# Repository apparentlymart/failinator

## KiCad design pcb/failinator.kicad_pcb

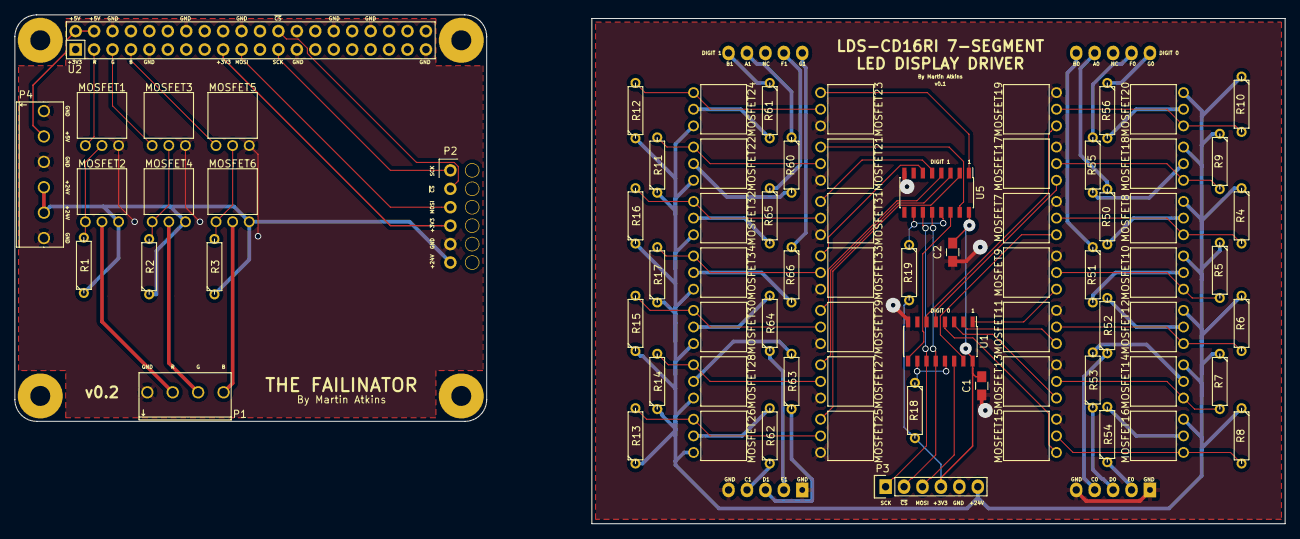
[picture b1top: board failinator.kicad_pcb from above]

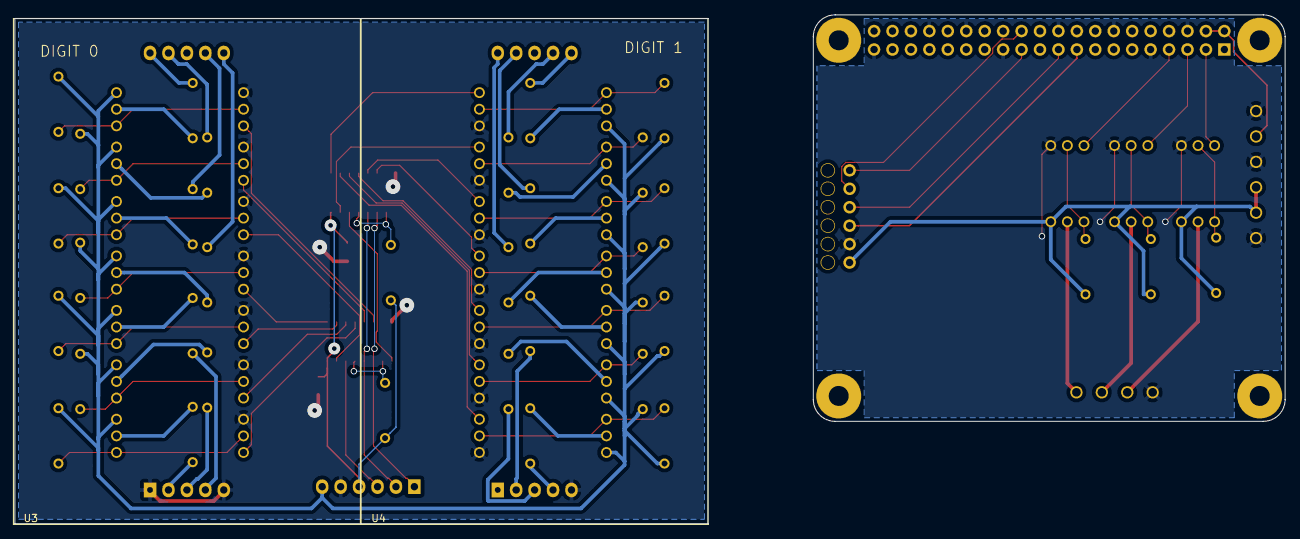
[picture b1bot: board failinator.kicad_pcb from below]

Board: 2 copper layers, 175.0 x 70.1 mm, 82 parts (2 on the bottom side), 81 nets.

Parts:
C1, C2: C_Small; C_0805_HandSoldering
MOSFET1, MOSFET3, MOSFET5, MOSFET7, MOSFET9, MOSFET11, MOSFET13, MOSFET15, MOSFET17, MOSFET19, MOSFET21, MOSFET23, MOSFET25, MOSFET27, MOSFET29, MOSFET31, MOSFET33: FQU13N06L; TO-251AA
MOSFET2, MOSFET4, MOSFET6, MOSFET8, MOSFET10, MOSFET12, MOSFET14, MOSFET16, MOSFET18, MOSFET20, MOSFET22, MOSFET24, MOSFET26, MOSFET28, MOSFET30, MOSFET32, MOSFET34: FQU17P06; TO-251AA
Mounting_Hole_2.75mm, Mounting_Hole_2.75mm#2, Mounting_Hole_2.75mm#3, Mounting_Hole_2.75mm#4: VAL**; Mounting_Hole_2.75mm
P1: CONN_01X04; TERM_4
P2: CONN_01X06; Wire_Conn_6pin_StrainReliefRight
P3: CONN_01X06; Pin_Header_Straight_1x06
P4: CONN_01X06; TERM_6
R1, R2, R3, R4, R5, R6, R7, R8, R9, R10, R11, R12, R13, R14, R15, R16, R17, R18, R19: 10k; R3
R50, R51, R52, R53, R54, R55, R56, R60, R61, R62, R63, R64, R65, R66: 150; R3
U1, U5: 74HC594; SOIC-16_3.9x9.9mm_Pitch1.27mm
U2: RASPIPLUSHEADER; Pin_Header_Straight_2x20
U3, U4: LDS-CD16RI

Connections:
+3V3: P2.4, U2.1, U2.17
+5V: P4.2, U2.2, U2.4
+24V: MOSFET2.3, MOSFET4.3, MOSFET6.3, P2.6, P4.4, P4.5, R1.1, R2.1, R3.1
/AmberDriver/EN: MOSFET3.1, U2.5
/AmberDriver/VOUT: MOSFET4.2, P1.3
/DISP_CS: P2.2, U2.24
/D_+3V3: C1.2, C2.2, P3.4, R18.2, R19.2, U1.16, U5.16
/D_DISP_CS: P3.2, U1.12, U5.12
/D_MOSI: P3.3, U1.14
/D_SCLK: P3.1, U1.11, U5.11
/DisplayDrivers/A0Driver/VOUT: MOSFET8.2, R50.2
/DisplayDrivers/A0_L: MOSFET7.1, U1.15
/DisplayDrivers/A0_P: R50.1, U3.7
/DisplayDrivers/A1Driver/VOUT: MOSFET22.2, R60.2
/DisplayDrivers/A1_L: MOSFET21.1, U5.15
/DisplayDrivers/A1_P: R60.1, U4.7
/DisplayDrivers/B0Driver/VOUT: MOSFET10.2, R51.2
/DisplayDrivers/B0_L: MOSFET9.1, U1.1
/DisplayDrivers/B0_P: R51.1, U3.6
/DisplayDrivers/B1Driver/VOUT: MOSFET24.2, R61.2
/DisplayDrivers/B1_L: MOSFET23.1, U5.1
/DisplayDrivers/B1_P: R61.1, U4.6
/DisplayDrivers/C0Driver/VOUT: MOSFET12.2, R52.2
/DisplayDrivers/C0_L: MOSFET11.1, U1.2
/DisplayDrivers/C0_P: R52.1, U3.4
/DisplayDrivers/C1Driver/VOUT: MOSFET26.2, R62.2
/DisplayDrivers/C1_L: MOSFET25.1, U5.2
/DisplayDrivers/C1_P: R62.1, U4.4
/DisplayDrivers/D0Driver/VOUT: MOSFET14.2, R53.2
/DisplayDrivers/D0_L: MOSFET13.1, U1.3
/DisplayDrivers/D0_P: R53.1, U3.3
/DisplayDrivers/D1Driver/VOUT: MOSFET28.2, R63.2
/DisplayDrivers/D1_L: MOSFET27.1, U5.3
/DisplayDrivers/D1_P: R63.1, U4.3
/DisplayDrivers/E0Driver/VOUT: MOSFET16.2, R54.2
/DisplayDrivers/E0_L: MOSFET15.1, U1.4
/DisplayDrivers/E0_P: R54.1, U3.2
/DisplayDrivers/E1Driver/VOUT: MOSFET30.2, R64.2
/DisplayDrivers/E1_L: MOSFET29.1, U5.4
/DisplayDrivers/E1_P: R64.1, U4.2
/DisplayDrivers/F0Driver/VOUT: MOSFET18.2, R55.2
/DisplayDrivers/F0_L: MOSFET17.1, U1.5
/DisplayDrivers/F0_P: R55.1, U3.9
/DisplayDrivers/F1Driver/VOUT: MOSFET32.2, R65.2
/DisplayDrivers/F1_L: MOSFET31.1, U5.5
/DisplayDrivers/F1_P: R65.1, U4.9
/DisplayDrivers/G0Driver/VOUT: MOSFET20.2, R56.2
/DisplayDrivers/G0_L: MOSFET19.1, U1.6
/DisplayDrivers/G0_P: R56.1, U3.10
/DisplayDrivers/G1Driver/VOUT: MOSFET34.2, R66.2
/DisplayDrivers/G1_L: MOSFET33.1, U5.6
/DisplayDrivers/G1_P: R66.1, U4.10
/DisplayDrivers/GND: C1.1, C2.1, MOSFET7.3, MOSFET9.3, MOSFET11.3, MOSFET13.3, MOSFET15.3, MOSFET17.3, MOSFET19.3, MOSFET21.3, MOSFET23.3, MOSFET25.3, MOSFET27.3, MOSFET29.3, MOSFET31.3, MOSFET33.3, P3.5, U1.8, U3.1, U3.5, U4.1, U4.5, U5.8
/DisplayDrivers/VIN: MOSFET8.3, MOSFET10.3, MOSFET12.3, MOSFET14.3, MOSFET16.3, MOSFET18.3, MOSFET20.3, MOSFET22.3, MOSFET24.3, MOSFET26.3, MOSFET28.3, MOSFET30.3, MOSFET32.3, MOSFET34.3, P3.6, R4.1, R5.1, R6.1, R7.1, R8.1, R9.1, R10.1, R11.1, R12.1, R13.1, R14.1, R15.1, R16.1, R17.1
/GreenDriver/EN: MOSFET5.1, U2.7
/GreenDriver/VOUT: MOSFET6.2, P1.4
/MOSI: P2.3, U2.19
/RedDriver/EN: MOSFET1.1, U2.3
/RedDriver/VOUT: MOSFET2.2, P1.2
/SCLK: P2.1, U2.23
GND: MOSFET1.3, MOSFET3.3, MOSFET5.3, P1.1, P2.5, P4.1, P4.3, P4.6, U2.6, U2.9, U2.14, U2.20, U2.25, U2.30, U2.34, U2.39
unnamed: MOSFET1.2, MOSFET2.1, R1.2
unnamed: MOSFET3.2, MOSFET4.1, R2.2
unnamed: MOSFET5.2, MOSFET6.1, R3.2
unnamed: MOSFET7.2, MOSFET8.1, R4.2
unnamed: MOSFET9.2, MOSFET10.1, R5.2
unnamed: MOSFET11.2, MOSFET12.1, R6.2
unnamed: MOSFET13.2, MOSFET14.1, R7.2
unnamed: MOSFET15.2, MOSFET16.1, R8.2
unnamed: MOSFET17.2, MOSFET18.1, R9.2
unnamed: MOSFET19.2, MOSFET20.1, R10.2
unnamed: MOSFET21.2, MOSFET22.1, R11.2
unnamed: MOSFET23.2, MOSFET24.1, R12.2
unnamed: MOSFET25.2, MOSFET26.1, R13.2
unnamed: MOSFET27.2, MOSFET28.1, R14.2
unnamed: MOSFET29.2, MOSFET30.1, R15.2
unnamed: MOSFET31.2, MOSFET32.1, R16.2
unnamed: MOSFET33.2, MOSFET34.1, R17.2
unnamed: R18.1, U1.10, U1.13
unnamed: R19.1, U5.10, U5.13
unnamed: U1.9, U5.14

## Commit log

2015-09-25 KiCad project.
2015-09-25 Schematic
2015-09-25 Pi Hat PCB mounting hole footprint.
2015-09-25 Project-specific footprint library.
2015-09-25 Component footprint assignments and netlist.
2015-09-25 Initial PCB floorplan.
2015-09-25 Swap the external lamp connections for easier PCB routing.
2015-09-25 Design rules and ground pour.
2015-09-25 PCB tracks.
2015-09-25 Silkscreen annotations.
2015-09-25 Change LED display pinout for a different display.
    The other display was too expensive, so switching to a smaller one.
2015-09-25 Re-fill polygons.
2015-10-07 Readme for the client
2015-10-08 Client that accepts notifications and updates the lights.
    Digits not working yet.
2015-10-09 first pass at ws server and test clients
2015-10-09 webhooks & website
    - added a new webhooks endpoint to receive VO events
    - more website styling
    - trigger events from the website
    - switch website to jquery
    - turn off ws test client writes
    - fix some event logic
2015-10-11 remove test webhooks. add webhook GET error response.
2016-01-02 CircuitJS model of new 7seg display driver design.
2016-01-02 Starting work on revision v0.2.
2016-01-02 Random library cache updates I didn't ask for
2016-01-02 Factor out the MOSFET switches into a separate sheet.
    There will be a lot more of these soon once we start using a similar
    pattern to switch the LED segments.
2016-01-02 Remove the MAX7219-based digit driver sub-circuit
    The digit driver on v0.1 was not correct, providing only 5V to LED
    segments that have a forward voltage of more like 27V, causing them to
    not show at all.
    A replacement for this will be added in a subsequent commit.
2016-01-02 Schematic symbol for 7-segment LED display
2016-01-02 Squeeze schematic layout to make more space.
    The 7 segment LED driver sub-circuits are going to take up a bunch of
    space.
2016-01-02 7-segment LED displays and their ground connections
2016-01-02 KiCad's ongoing fiddling with the shared component refs
    When using the same child schematic sheet multiple times, KiCad keeps
    updating the references to point to the last one that was viewed/edited.
    So this change doesn't actually do anything.
2016-01-02 Connect the LED controller CS to RPi pin 24.
    In the v0.1 design this was erroneously connected to pin 22, which is not
    supported as a hardware SPI chip select. Pin 24 is SPI0_CE0_N, which is
    the chip select pin for the first (zeroth) SPI device on the primary SPI
    bus.
2016-01-02 Tweak layout of the "Status Lamp Control" area
    Just a minor cosmetic tweak to improve the visual balance.
2016-01-02 Title on the MOSFETDriver sheet
2016-01-02 Random updates to the KiCad project file
2016-01-11 MOSFET driver circuits for the 7-segment displays
2016-01-11 74HC594 schematic symbol
2016-01-11 Shift registers for the 7-seg displays
2016-02-21 Display board connects via 6-wire connector
2016-02-21 MOSFET resistor numbering
2016-02-21 Shift register decoupling caps
2016-02-21 Some footprint assignments
2016-02-21 Remaining footprint assignments
2016-02-21 Start of 7seg display board floor planning
2016-02-21 Use through-hole footprints for all display board resistors
    Previously two of them were incorrectly set to 0805 SMD footprints.
    I actually expect the display board layout is going to be very cramped
    so these might actually all become 0805s later, but going to try with
    through-hole first because I don't relish the thought of hand-soldering
    14 0805 resistors in a single sitting.
2016-02-21 Placement of display 0 MOSFETs and resistors
2016-02-21 Initial work on traces for digit 0's MOSFETs
2016-02-21 Ground plane for the LED display board
2016-02-21 Shift register data connections
2016-02-21 Digit 0 LED segment power traces
2016-02-21 Shift register decoupling capacitors
2016-02-21 Main board traces to the display board connector
2016-02-21 Current-limiting resistors on the display segments
    Missed these on the first pass because I copied the drivers from the
    RYG tower but forgot that they have integrated resistors.
2016-02-21 Rework digit 0 layout for current-limiting resistors
2016-02-21 Place some grounds better so they are in the main copper pour
2016-02-21 Placement of components for digit 1
2016-02-21 Digit 1 traces
2016-02-21 Move the 7seg display board into a more sensible position
2016-02-21 Silkscreen title
2016-02-22 Silkscreen labels for the various connections
2016-02-22 Possibly overboard on the silkscreen labels
    The complete lack of labels last time made debugging difficult, so I'm
    now going to the other extreme of labeling basically everything in case
    we end up needing to attach probes or do more bodging this time around.
2016-05-30 Adjust for the shift register on the v0.2 board
    This replaces the dedicated Maxim LED driver IC with an 8-bit shift
    register with a bunch of MOSFETs, so that the digits can be driven at
    24V rather than just 5V.
